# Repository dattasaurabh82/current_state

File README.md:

# World Theme Music Player

<p align="left">
  If you find this project useful, consider supporting its development <br><br>

</p>

---
<br>

> **An AI-powered ambient music generator that transforms daily world news into mood-based soundscapes. Designed to sit on top of IKEA FREKVANS SPEAKERS, this will trigger playback of AI generated soundscape/music when a person enters a room or a motion is detected. So a suitable place for this are contemplation rooms like bathrooms 🙃**

<br>

*What does it look like?*

*Monitor Web Dashboard*

The main functionality of the system is to fetch news headlines from multiple regions, analyze their emotional tone using an LLM, select musical archetypes, and generate unique ambient music — all running autonomously on a Raspberry Pi using open-source LLM models hosted on [Replicate](https://replicate.com/). 
With onboard hardware buttons, all functionalities can be triggered and controlled. For example,  disabling radar trigger or shutting down or turning ON the PI or even resetting WiFi for the PI, can all be carried out via the custom PI HAT I designed! (More on that later ...) 

---

## Table of Contents

- [What it does (Summary)?](#what-it-does-summary)
- [Other features](#other-features)
- [What can you do?](#what-can-you-do)
- [How It Works](#how-it-works)
- [Prerequisites](#prerequisites)
  - [Hardware](#1-hardware)
  - [API Accounts](#2-api-accounts)
- [Summary of steps to take](#summary-of-steps-need-to-take-action)
  - [Step 1: Mandatory Update](#step-1-installation-and-basic-setup-mandatory-update)
  - [Step 2: Configuration Reference](#step-2-installation-and-basic-setup-understand-the-configuration-reference)
  - [Step 3: Run Setup Script](#step-3-run-setup-script)
  - [Step 4: Hardware Testing](#step-4-hardware-testing)
  - [Step 5: Installing WiFi Manager](#step-5-installing-wifi-manager)
  - [Step 6: Test Full Pipeline](#step-6-test-full-pipeline)
  - [Step 7: Services Installation](#step-7-services-installation)
- [Web Dashboard](#web-dashboard)
- [Project Structure](#project-structure)
- [License](#license)
- [Supporting Docs](#supporting-docs)
- [Manual Setup (Archive)](#archive-manual-setup-instructions)
- [TODO](#todo)

---

## What it does (Summary)?

- Every night at 3:00 AM, scrapes news and generates a 30-second ambient music piece based on world sentiment (and various other factors)
- Then, if the device detects presence of a person (also notified via LED), it plays back that music in a loop for a predefined time (currently set to 5 mins) and then stops
- While music is playing, the LED is ON. While paused, it turns OFF
- It serves a web monitor where you can see:
  - News Tab: News that were collected
  - Pipeline Tab: view explaining how music was then generated including Music files too
  - Logs Tab: of all process for live preview and debugging of any steps
- If fails to connect to Wifi, it blinks and notifies you
- If any step in the full pipeline (news scraping -> music generation) it shows in logs and if radar detection is disabled the LED also notifies you with blinks

## Other features

- Smart log management and lot of configuration settings
- It also comes with smart installation and uninstallation scripts, detailed documentation and maintenance instructions
- **Optional and not included in documentation**, but it can automatically upload music and crucial data for future analysis, to drop box as well as locally

## What can you do?

- With the press of a button you can turn the system on & off
- With the press of a button you can headlessly setup it's wifi, over a browser
- You can manually trigger the full pipeline: news scraping -> music generation
- You can play/pause and stop the music with buttons
- You can enable or disable radar detection
- You can run tests to understand how the pipeline works
- **Optional and not included in documentation**, but you can also manually backup with a single cmd or set it to do it automatically 

## How It Works

The system has two modes of operation:

### Pipeline Overview

The **automated pipeline** runs daily at 3:00 AM:

> [!Note]
> This 3:00 AM is defined in cronjob settings which can be manually altered but it is defined in the [services/01_install_and_start_services.sh](services/01_install_and_start_services.sh)

| Stage | What Happens |
|-------|--------------|
| **Fetch** | NewsAPI provides headlines in 4 languages (EN, DE, FR, ES) — 4 API requests total |
| **Analyze** | Llama 3 70B extracts mood: valence (-1 to +1), tension (0-1), hope (0-1), energy level |
| **Select** | Rule-based scoring matches the mood profile to one of 6 musical archetypes |
| **Build** | Three-layer prompt construction: archetype structure + theme textures + daily variety |
| **Generate** | MusicGen stereo-melody-large creates a 30-second ambient piece |
| **Process** | Fade-in (1.5s) and fade-out (2s) are applied |

The **user-triggered interactions** happen via hardware:

| Trigger | Action |
|---------|--------|
| **GPIO17 Button** | Manually triggers the full news→music pipeline |
| **Radar Motion** | Starts looping playback when presence is detected (see [Radar Behavior](#radar-behavior)) |
| **Radar Enable Switch** | GPIO6 toggle — when ON, radar controls playback; when OFF, radar is ignored |
| **Play/Pause Button** | Toggle playback state |
| **Stop Button** | Stop playback completely |

---

## Prerequisites

### 1. Hardware

| ASSEMBLY RENDER | PCB RENDER |
| --- | --- |
|  |  | 

#### Schematic 

>[!Important]
> Click on the ☝🏻 image to see the [detailed schematic](docs/pi-hat-schematic.pdf)

**Project HW Requirements** (_Highlights_):

- Raspberry pi 3A+ (with 32GB or more micro SD card or storage)
- IKEA FREKVANS Speaker: Find them in eBay
- Short audio cable male-male 3.5 mm
  - Extra Custom PCB for Fingerbot (Extra & Optional)
- [MeanWell RS-15-5 15W 5V 3A Power Supply Module](https://amzn.eu/d/2xTGYza): AC to 5V power supply (internal) for powering the PI from the daily chained power supply, coming from the speakers
- mmWave Radar: [Rd-03D Serial mmWave RADAR](https://amzn.eu/d/4WUBDUL) (_Recommended_) or [RCWL-0516 Switching mmWave RADAR](https://amzn.eu/d/39ujNUH) or both (🙃)
- Custom PI-HAT
- Custom 3D prints

>[!Note]
> For the full assembled product details reach out to hi@dattasaurabh.com 

---

### 2. API Accounts

Before running the setup script, create accounts and gather these credentials:

| Service | What You Need | Where to Get It |
|---------|---------------|-----------------|
| **NewsAPI** | API Key | [newsapi.org/account](https://newsapi.org/account) → Generate API Key |
| **Replicate** | API Token | [replicate.com/account/api-tokens](https://replicate.com/account/api-tokens) |

> [!TIP]
> **Keep these credentials handy** — you'll need them when running `setup.sh` in the next section.

#### Cost Breakdown

| Service | Plan | Usage | Cost |
|---------|------|-------|------|
| **NewsAPI** | Free tier (100 requests/day) | 4 requests/day (one per language) | **Free** |
| **Replicate** | Pay-per-use | ~1 generation/day | **~$3/month** |

**Replicate cost details:**
- MusicGen runs on Nvidia A100 (80GB) @ $0.00140/sec — typical generation takes ~50-60 seconds = ~$0.07-0.08
- Llama 3 70B runs on Nvidia A100 (80GB) @ $0.00140/sec — typical analysis takes ~10-15 seconds = ~$0.01-0.02
- **Total per generation: ~$0.08-0.10**

**NewsAPI notes:**
- Uses the `/everything` endpoint to fetch recent articles
- Free tier provides access to articles from the previous day
- Once set to run autonomously, our system makes only 4 requests daily (one per language: EN, DE, FR, ES), well under the 100/day limit

---

## Summary of steps need to take action

> Once you have the HW ready, here's what needs to be done ...

1. Basic Pi setup (update packages)
2. Understand configuration options
3. Run setup script (handles most installation and configuration automatically)
4. Reboot
5. Test hardware
6. Install WiFi manager (optional)
7. Test full pipeline
8. Deploy services

---

### Step 1: Installation and basic setup: Mandatory Update

```bash
sudo apt-get update -y
sudo apt-get upgrade -y
```

After that, reboot. 

---

### Step 2: Installation and basic setup: Understand the Configuration Reference

> [!Note]
> Familiarize yourself with the configuration files. Many of these will be prompted to you during running the helper setup script (below), but understanding them is also important later testing steps.

> In `settings.json` (you may only see now `settings.json.template`)

Controls GPIO pins, hardware behavior, and feature settings:

```json
{
  "inputPins": {
    "playPauseBtnPin": 22,
    "stopBtnPin": 27,
    "runFullCycleBtnPin": 17,
    "radarEnablePin": 6,
    "radarModel": "RCWL-0516",
    "radarPin": 16
  },
  "outputPins": {
    "playerStateLEDPin": 25,
    "radarStateLEDPin": 23
  },
  "hwFeatures": {
    "btnDebounceTimeMs": 0.05,
    "maxLEDBrightness": 25,
    "pauseBreathingFreq": 0.25,
    "motionTriggeredPlaybackDurationSec": 300,
    "cooldownAfterUserActionSec": 60,
    "radarMaxRangeMeters": 2.5,
    "radarTargetTimeoutSec": 1.0
  },
  "music": {
    "fadeInDurationSec": 1.5,
    "fadeOutDurationSec": 2.0
  }
}
```

#### 0. Key Settings Explained `settings.json`

> [!Note]
> The setup script, if ran will update few of these values after asking you and others will remain fixed, especially Hardware ones. But you can also manually create settings file (`cp settings.json.template settings.json`) and edit some of these, if you know what you are doing 🙃. The below explanation thus aims to provide some clarity.     

| Setting | Default | Description |
|---------|---------|-------------|
| `radarEnablePin` | 6 | GPIO pin for radar enable switch — when HIGH, radar triggers playback |
| `radarModel` | `RCWL-0516` | Radar type: `RCWL-0516` (GPIO) or `RD-03D` (Serial UART) |
| `motionTriggeredPlaybackDurationSec` | 300 | How long music plays after motion detected (5 minutes) |
| `cooldownAfterUserActionSec` | 60 | After user presses pause/stop, radar is ignored for this duration |
| `radarMaxRangeMeters` | 2.5 | Detection range (`RD-03D` only) |
| `radarPin` | 16 | GPIO pin to which radar `RCWL-0516` is connected. Not used by radar `RD-03D` as it operates over Serial  |
| `maxLEDBrightness` | 25 | LED brightness (0-100) |

**Notes on diff radars used**: ...

| Radar Model | How to Identify? | Setting | Notes |
| --- | --- | --- | --- |
| [Rd-03D Serial mmWave RADAR](https://amzn.eu/d/4WUBDUL) |  | `"radarEnablePin": 6` <br>`"radarModel": "RD-03D"` | You can leave `"radarPin": 16` in settings but this radar uses PI's Serial PINs and the script will ignore this setting |
| [RCWL-0516 Switching mmWave RADAR](https://amzn.eu/d/39ujNUH) |  | `"radarEnablePin": 6` <br>`"radarModel": "RCWL-0516"`<br>`"radarPin": 16` | `GPIO 16` receives HIGH or LOW based on motion detection |

#### 1. `news_config.json`

> [!Warning]
> Do not change these

Configures which language regions to fetch news from:

```json
{
  "regions": {
    "English_Speaking": { "language": "en" },
    "German_Speaking": { "language": "de" },
    "French_Speaking": { "language": "fr" },
    "Spanish_Speaking": { "language": "es" }
  }
}
```

> [!Note]
> More regions will be included in the future

#### 2. `.env`

API credentials:

```bash
NEWS_API_KEY="your_newsapi_key"
REPLICATE_API_TOKEN="your_replicate_token"
```

>[!Note]
> Will be set by setup script, if ran and here only for reference. 
> If setup script is not ran, then copy [.env.template](.env.template) to `.env` (`cp copy .env.template copy .env`) and you can add them manually. 

---

### Step 3: Run Setup Script

The setup script automates the entire installation process.

#### First Time Installation (via curl)

```bash
curl -fsSL https://raw.githubusercontent.com/dattasaurabh82/current_state/main/setup.sh | bash
```

Or using wget:

```bash
wget -qO- https://raw.githubusercontent.com/dattasaurabh82/current_state/main/setup.sh | bash
```

#### Re-running Setup (after clone)

If you've already cloned the repository, you can re-run setup locally:

```bash
cd ~/current_state
./setup.sh
```

#### What the Setup Script Does

| Step | Description |
|------|-------------|
| **System Check** | Verifies Raspberry Pi and internet connectivity |
| **Date/Time Sync** | Enables NTP and syncs system clock automatically |
| **System Dependencies** | Installs build tools, libraries (`build-essential`, `libssl-dev`, etc.) |
| **Audio Dependencies** | Installs PortAudio (`libportaudio2`) |
| **UV Package Manager** | Installs [UV](https://github.com/astral-sh/uv) for Python dependency management |
| **GPIO Permissions** | Adds user to `gpio` group |
| **Clone Repository** | Clones project to `~/current_state` (or pulls latest if exists) |
| **Python Dependencies** | Runs `uv sync` to install all Python packages |
| **Hostname** | Sets hostname to `aimusicplayer` (access via `aimusicplayer.local`) |
| **Console Auto-login** | Enables auto-login for user services to start on boot |
| **I2C Disable** | Disables I2C to free GPIO3 for power button |
| **Serial Enable** | Enables serial hardware for RD-03D radar, disables serial console |
| **GPIO Shutdown** | Adds `dtoverlay=gpio-shutdown` to config.txt for power button |
| **Hardware Settings** | Interactive prompts for radar model, playback duration, LED brightness → creates `settings.json` |
| **API Credentials** | Interactive prompts for NewsAPI key and Replicate token → creates `.env` |

> [!IMPORTANT]
> After setup completes, **REBOOT is required** for hostname, I2C, serial, and GPIO shutdown changes to take effect.

---

### Step 4: Hardware Testing

Before installing services, test each component individually to verify wiring and configuration.

> [!NOTE]
> If you installed the WiFi Manager (explained below), **stop it first** before testing buttons and LEDs:
> ```bash
> sudo systemctl stop rpi-btn-wifi-manager.service
> ```

#### Test GPIO Buttons & LEDs

```bash
uv run python tests/01_test_IOs.py
```

**What to expect:**
- Press each button and observe console output confirming the press
- LEDs should light up when tested

**Pins being tested:**

| Component | GPIO |
|-----------|------|
| Play/Pause Button | 22 |
| Stop Button | 27 |
| Full Cycle Button | 17 |
| Radar Enable Switch | 6 |
| Player State LED | 25 |
| Radar State LED | 23 |

#### Test Radar Detection

The radar sensor enables automatic, presence-triggered playback. This is useful for installation scenarios where you want music to play when someone approaches.

| Radar Model | Interface | Best For |
|-------------|-----------|----------|
| `RCWL-0516` | GPIO (digital HIGH/LOW) | Simple presence detection |
| `RD-03D` | Serial (UART) | Distance-based detection with configurable range |

> [!Warning]
> Ensure your radar model is set correctly according to your HW setup in `settings.json` (as explained above)

Run the appropriate tests:

**- For `RCWL-0516` (GPIO-based)**

```bash
uv run python tests/02_test_event_radar.py
```

**What to expect:**
- Walk in front of the sensor
- Console shows "Motion detected" / "Motion stopped"
- Radar LED (GPIO 23) lights up during detection

**- For `RD-03D` (Serial-based)**

```bash
uv run python tests/02_test_serial_radar.py
```

**What to expect:**
- Walk in front of the sensor
- Console shows motion waveform

**- For `RD-03D` (Serial-based _but designed for outputting events_)**

```bash
uv run python tests/03_test_serial_radar_as_event.py
```

**What to expect:**
- Walk in front of the sensor
- Console shows "Motion detected" / "Motion stopped"
- Radar LED (GPIO 23) lights up during detection

#### Tuning RD-03D Radar Detection

The RD-03D radar can produce **false triggers in empty rooms**. This happens because its Kalman filter causes the reported distance to oscillate in a slow wave pattern (e.g. 6m → 2m → 6m over ~10 seconds). When the wave dips below `radarMaxRangeMeters`, the old logic counted it as motion.

The detection algorithm now uses a **stability filter** that requires multiple consecutive in-range readings with stable (clustered) distances before triggering. This eliminates false triggers from the oscillating wave while still detecting real people within ~500ms.

**Tunable constants** are at the top of `lib/radar_controller.py`:

| Constant | Default | What it does |
|----------|---------|-------------|
| `RD03D_CONSECUTIVE_READINGS_REQUIRED` | 5 | How many in-range readings in a row before triggering. Higher = fewer false triggers but slower detection. |
| `RD03D_MAX_DISTANCE_STD_DEV` | 0.4 | Max allowed standard deviation (meters) across those readings. Lower = stricter, rejects more noise. |

**If you get false triggers in an empty room:**
- Increase `RD03D_CONSECUTIVE_READINGS_REQUIRED` (try 7 or 8)
- Decrease `RD03D_MAX_DISTANCE_STD_DEV` (try 0.3)
- Decrease `radarMaxRangeMeters` in `settings.json` (try 2.0)

**If real people are not detected:**
- Decrease `RD03D_CONSECUTIVE_READINGS_REQUIRED` (try 3 or 4)
- Increase `RD03D_MAX_DISTANCE_STD_DEV` (try 0.5 or 0.6)

**How to debug:**

```bash
cd ~/current_state/tests

# Raw data view — see every field the radar reports
uv run 04_test_radar_diagnostics.py

# Filter comparison — runs OLD vs STABLE logic side by side
uv run 04_test_radar_diagnostics.py --filter
```

In raw mode, observe:
- Empty room: lots of `·` (out of range), occasional `✓` that dips in and out = normal wave noise
- Person present: sustained blocks of `✓` with stable distances = real detection

In filter mode, observe:
- `OLD` triggers in empty room = the bug
- `STABLE` does not trigger in empty room = fix working
- `STABLE` triggers when you walk in = detection still works

> [!Important]
> Later when the **Radar Enable Switch** (GPIO 6) is ON:
> 
> 1. **Motion detected** → Music starts playing in a loop
> 2. **Music plays for 5 minutes** (configurable: `motionTriggeredPlaybackDurationSec`)
> 3. **No motion for 5 min** → Music auto-stops
> 4. **Motion detected again** → Playback resumes

> [!Note]
> **Cooldown behavior:** If a user manually presses **Pause** or **Stop**, the radar is temporarily ignored for 60 seconds (configurable: `cooldownAfterUserActionSec`). This prevents the radar from immediately restarting playback after a deliberate user action.

#### Test Audio Output

Verify the speaker/audio output is working:

```bash
aplay keep_audio_ch_active.wav
```

**What to expect:** You should hear a short tone.

---

### Step 5: Installing WiFi Manager

For headless WiFi configuration without monitor/keyboard, install and configure this project:[rpi-wifi-configurator](https://github.com/dattasaurabh82/rpi-wifi-configurator).

> [!IMPORTANT]
> Install/enable/setup WiFi Manager **after** hardware testing!

#### Step 5.1: Installing WiFi Manager: How it will Work

0. If PI, could not connect to WiFi, you will see the Status LED Blink ... or you can also remove the front panel to long press the network reset button 
1. **Long press** the WiFi reset button (>4 sec)
2. Pi creates an Access Point (`RPI_NET_SETUP`) (_This is Default but you can change during installation, just follow the prompts. But I would recommend not to change_)

| | | | |
| --- | --- | --- | --- |
|  |  |  |  |

1. Connect your phone/laptop to that AP
2. Navigate to `http://10.10.1.1:4000`
3. Enter your WiFi SSID and password
4. Pi connects to your network: NET Status LED breathes and then turns solid for a bit and then turns off completely.

> [!Note]
> You can checkout this project ([rpi-wifi-configurator](https://github.com/dattasaurabh82/rpi-wifi-configurator)) more in details to understand how it works.

#### Step 5.2: Installing WiFi Manager: The actual Installation Process

```bash
curl -fsSL https://raw.githubusercontent.com/dattasaurabh82/rpi-wifi-configurator/main/install.sh | bash
```

> [!Important]
During setup, enter these GPIO settings for this project, as below:

| Setting | Value | Notes |
|---------|-------|-------|
| Button GPIO | **26** | `NET_RESET_BTN` — dedicated WiFi reset button |
| LED GPIO | **24** | `LED_NET` - dedicated WiFI status LED  |

### Network LED Status Indicators

| LED State | Pattern | Meaning |
|-----------|---------|---------|
| **OFF** | No light | Connected to WiFi (normal operation) |
| **SLOW BREATH** | Smooth pulse | Searching for WiFi / attempting connection |
| **FAST BLINK** | Quick on/off | AP mode active (ready for configuration) |
| **SOLID → OFF** | 2 sec solid | Connection successful |

#### Step 5.3: Stopping for Hardware Tests

If you are running hardware tests, stop the WiFi manager service to free up `GPIO 24` and `GPIO 26`

```bash
sudo systemctl stop rpi-btn-wifi-manager.service
```

After testing, you can restart it:

```bash
sudo systemctl start rpi-btn-wifi-manager.service
```

---

### Step 6: Test Full Pipeline

#### Step 6.1: Test Full Pipeline: Generate music without playback to verify API connectivity

> [!Warning]
> For this to work properly make sure you have the `.env` file with correct settings (keys). As said before, you will be prompted to fill in the keys during installation. So there's some prep work but you can also always manually add them after you understand, from above, what is required in this `.env` file and why

```bash
uv run python main.py --fetch true --play false
```

**What to expect:**
- News headlines are fetched and cached to `news_data_YYYY-MM-DD.json`
- LLM analyzes mood (takes ~10-20 seconds)
- MusicGen generates audio (takes ~50-60 seconds)
- Output music saved to `music_generated/world_theme_YYYY-MM-DD_HH-MM-SS.wav`
- Other metadata, to be used by web-monitor (more on that later), are saved in `generation_results/`

#### Step 6.2 (Optional): Test Full Pipeline: Test/Understand each part of news -> music strategy

> [!Note]
> You can also test individual parts to understand how the music gen prompt is created from news by following the guide  from [docs/MUSIC_PROMPT_GENERATION_PIPELINE.md](docs/MUSIC_PROMPT_GENERATION_PIPELINE.md)

#### Step 6.3: Test Full Pipeline: Test Hardware Player

Interactive test with keyboard controls:

```bash
uv run python run_player.py
```

**Controls:**

| Key | Action |
|-----|--------|
| `P` | Play / Pause |
| `S` | Stop |
| `Q` | Quit |

**What to expect:**
- Player finds the latest song in `music_generated/`
- Press `P` to play — LED goes solid
- Press `P` again to pause — LED breathes
- Press `S` to stop — LED turns off

For daemon mode (no keyboard, GPIO buttons only):

```bash
uv run python run_player.py --daemon
```

#### Step 6.4: Test Full Pipeline: Re-enable WiFi Manager

After testing, restart the WiFi manager if you installed it and disable it for hardware testing, let's say:

```bash
# Check status
sudo systemctl status rpi-btn-wifi-manager.service

# Ctrl+c or :q + ENTER may be required ...

sudo systemctl daemon reload
sudo systemctl start rpi-btn-wifi-manager.service
sudo systemctl status rpi-btn-wifi-manager.service

# Then if you are interested in checking the logs, you can:
# tail -F <PATH TO rpi-wifi-configurator>/logs/<LATEST LOG FILE>.log
```

---

### Step 7: Services Installation

Once hardware testing passes, install the background services.

#### Step 7.1: Services Installation: Check Current Status

```bash
./services/00_status.sh
```

#### Step 8.2: Services Installation: Install All Services

```bash
./services/01_install_and_start_services.sh
```

**This installs:**

| Service | Description |
|---------|-------------|
| `music-player.service` | Plays music, handles GPIO buttons, radar detection |
| `full-cycle-btn.service` | GPIO17 button triggers full news→music pipeline |
| `process-monitor-web.service` | Web dashboard on port 7070 |
| nginx | Reverse proxy (access dashboard on port 80) |

#### Step 7.3: Services Installation: Verify Installation

```bash
./services/00_status.sh
```

**Expected output:**

```
User Services

  ● full-cycle-btn.service
  ● music-player.service
  ● process-monitor-web.service

nginx

  ● nginx
  ● config installed
```

#### Step 7.4 (Good to Know): Services Installation: Uninstall Services

```bash
./services/04_stop_and_uninstall_services.sh
```

**What this removes:**
- User systemd services (stopped, disabled, files deleted)
- nginx site configuration
- Cron job for daily generation

**What this does NOT remove:**
- nginx itself (may be used by other sites)
- Project files (your code is safe)
- Generated music and logs

#### Services Scripts Reference

| Script | Purpose |
|--------|----------|
| `00_status.sh` | Check status of all services, nginx, and cron job |
| `01_install_and_start_services.sh` | Install and start all services + cron job |
| `04_stop_and_uninstall_services.sh` | Stop and remove all services + cron job |

#### Full Project Removal

To completely remove the project (services + files + dependencies):

```bash
./remove.sh
```

**What `remove.sh` offers (interactive):**

| Option | What it removes |
|--------|------------------|
| Services | Calls `04_stop_and_uninstall_services.sh` |
| Virtual environment | `.venv/` directory |
| Generated files | `music_generated/`, `logs/`, `generation_results/`, cache files |
| Project directory | Entire `current_state/` folder |
| UV | UV binary and cache (optional) |

> [!WARNING]
> `remove.sh` is interactive and asks for confirmation before each removal step.

#### Useful Commands

```bash
# Check individual service
systemctl --user status music-player.service

# Follow logs in real-time
journalctl --user -u music-player.service -f

# Manually trigger generation
uv run python main.py --fetch true --play false
```

---

## Web Dashboard

A TUI-style web interface for monitoring the pipeline from any device on your network.

### Features

| Tab | Description |
|-----|-------------|
| **News** | Today's headlines grouped by region (from cached JSON) |
| **Pipeline** | Interactive graph: mood analysis → archetypes → prompt components |
| **Logs** | Live streaming logs (like `tail -f` in your browser) |

### Access URLs

| Method | URL |
|--------|-----|
| Via nginx | `http://aimusicplayer.local` |
| Direct | `http://aimusicplayer.local:7070` |

### Where to Find Things

| What | Location |
|------|----------|
| Generated music | `music_generated/` |
| Today's news | `news_data_YYYY-MM-DD.json` |
| Pipeline results | `generation_results/pipeline_results.json` |
| Visualizations | `generation_results/visualizations/` |
| Logs | `logs/` |

📖 **Full documentation:** [`web/README.md`](web/README.md)

---

## Project Structure

```txt
├── README.md
├── LICENSE
├── pyproject.toml
├── uv.lock
├── main.py                      # Pipeline orchestrator
├── run_player.py                # Hardware player daemon
├── run_full_cycle_btn.py        # GPIO17 button handler
├── keep_audio_ch_active.wav     # Speaker keep-alive tone
├── settings.json                # Hardware & feature config (create from template)
├── news_config.json             # News regions config
├── .env                         # API credentials (create from template)
│
├── lib/                         # Core modules
│   ├── news_fetcher.py          # NewsAPI client
│   ├── llm_analyzer.py          # LLM mood extraction
│   ├── archetype_selector.py    # Rule-based archetype scoring
│   ├── music_prompt_builder.py  # 3-layer prompt construction
│   ├── music_generator.py       # MusicGen via Replicate
│   ├── music_post_processor.py  # Fade in/out
│   ├── player.py                # Audio playback engine
│   ├── hardware_player.py       # GPIO buttons, LEDs, radar
│   ├── radar_controller.py      # RCWL-0516 / RD-03D support
│   └── settings.py              # Settings loader
│
├── services/                    # Systemd service management
│   ├── 00_status.sh             # Check all services
│   ├── 01_install_and_start_services.sh
│   ├── 04_stop_and_uninstall_services.sh
│   └── *.service                # Service unit files
│
├── docs/                        # Documentation
│   ├── MUSIC_PROMPT_GENERATION_PIPELINE.md
│   └── pi-hat-schematic.pdf
│
├── web/                         # Dashboard (FastAPI + WebSocket)
├── tests/                       # Hardware test scripts
├── tools/                       # Utilities
├── logs/                        # Runtime logs
├── music_generated/             # Output audio files
├── generation_results/          # Pipeline outputs + visualizations
└── assets/                      # Documentation images
```

---

## License

[Unlicense](LICENSE)

---

## Supporting Docs:

1. [MUSIC_PROMPT_GENERATION_PIPELINE.md](docs/MUSIC_PROMPT_GENERATION_PIPELINE.md)
2. [Tests](tests)
3. [Web View Monitor](web/README.md)
4. [Hardware Schematic](_HW)

---

<details>
<summary><strong>Click to expand</strong> — Manual Setup Instructions - Reference for setup.sh development</summary>

### Manual Date/Time Setup

If NTP sync fails or you need to set timezone manually:

First, verify your Pi's date is correct:

```bash
date
```

If incorrect, fix via `raspi-config`:

```bash
sudo raspi-config
```

| Step | View |
|------|------|
| Select "Localisation Options" → ENTER |  |
| Select "Timezone" → ENTER |  |
| Select your region |  |

Tab to `<Finish>` and reboot:

```bash
sudo reboot
```

### Install System Dependencies

```bash
sudo apt update -y
sudo apt upgrade -y 
sudo apt install git -y 
sudo apt install build-essential libssl-dev zlib1g-dev libbz2-dev libreadline-dev libsqlite3-dev curl libncursesw5-dev xz-utils tk-dev libxml2-dev libxmlsec1-dev libffi-dev liblzma-dev jq tree -y
sudo apt install python3-dev -y
```

### Install Audio Dependencies

```bash
sudo apt-get install libportaudio2 -y
```

### Install UV

```bash
curl -LsSf https://astral.sh/uv/install.sh | sh
```

### GPIO Permissions

```bash
sudo usermod -a -G gpio $USER
sudo reboot
```

### Clone & Install

```bash
git clone https://github.com/YOUR_USERNAME/current_state.git
cd current_state
uv sync
```

If RPi.GPIO fails:
```bash
uv pip install RPi.GPIO --break-system-packages
```

### Create Environment File

```bash
cp .env.template .env
nano .env
```

Add your credentials:
```bash
NEWS_API_KEY="your_newsapi_key"
REPLICATE_API_TOKEN="your_replicate_token"
```

### Manual Service Installation (Legacy)

If not using the install script:

```bash
# Create user systemd directory
mkdir -p ~/.config/systemd/user

# Music Player
cp services/music-player.service ~/.config/systemd/user/
systemctl --user daemon-reload
systemctl --user enable --now music-player.service

# Full Cycle Button
cp services/full-cycle-btn.service ~/.config/systemd/user/
systemctl --user enable --now full-cycle-btn.service

# Enable linger (services run without login)
sudo loginctl enable-linger $USER
```

### Shutdown & Wake Button (GPIO3)

Enable hardware shutdown/wake using a dedicated button on GPIO3.

#### Step 1: Disable I2C

> [!WARNING]
> GPIO3 is shared with I2C SCL. You must disable I2C to use it for shutdown.

```bash
sudo raspi-config
```

| Step | View |
|------|------|
| Select *Interface Options* |  |
| Select *I2C* |  |
| Select *No* to disable |  |
| *Finish* and reboot |  |

#### Step 2: Enable gpio-shutdown Overlay

```bash
sudo nano /boot/firmware/config.txt
```

Add after the overlays comment section:

```ini
dtoverlay=gpio-shutdown
```

Reboot and test:
- Press GPIO3 button → Pi shuts down
- Press again → Pi wakes up

</details>

---

## TODO

- Add Dropbox backup details in readme (optional feature)
- ~~Serial Radar detection algo improvement~~ ✅ Stability filter (consecutive + std dev)

- 3rd attempt hardware update steps: 
  - 🟠 Speaker Switch switcher 
  - 🟠 Assemble new one ... 

**Future**:
- Add more news regions
- More archetypes
- Embedding models if needed
- Data viz after a period of time on the world sentiment shifts

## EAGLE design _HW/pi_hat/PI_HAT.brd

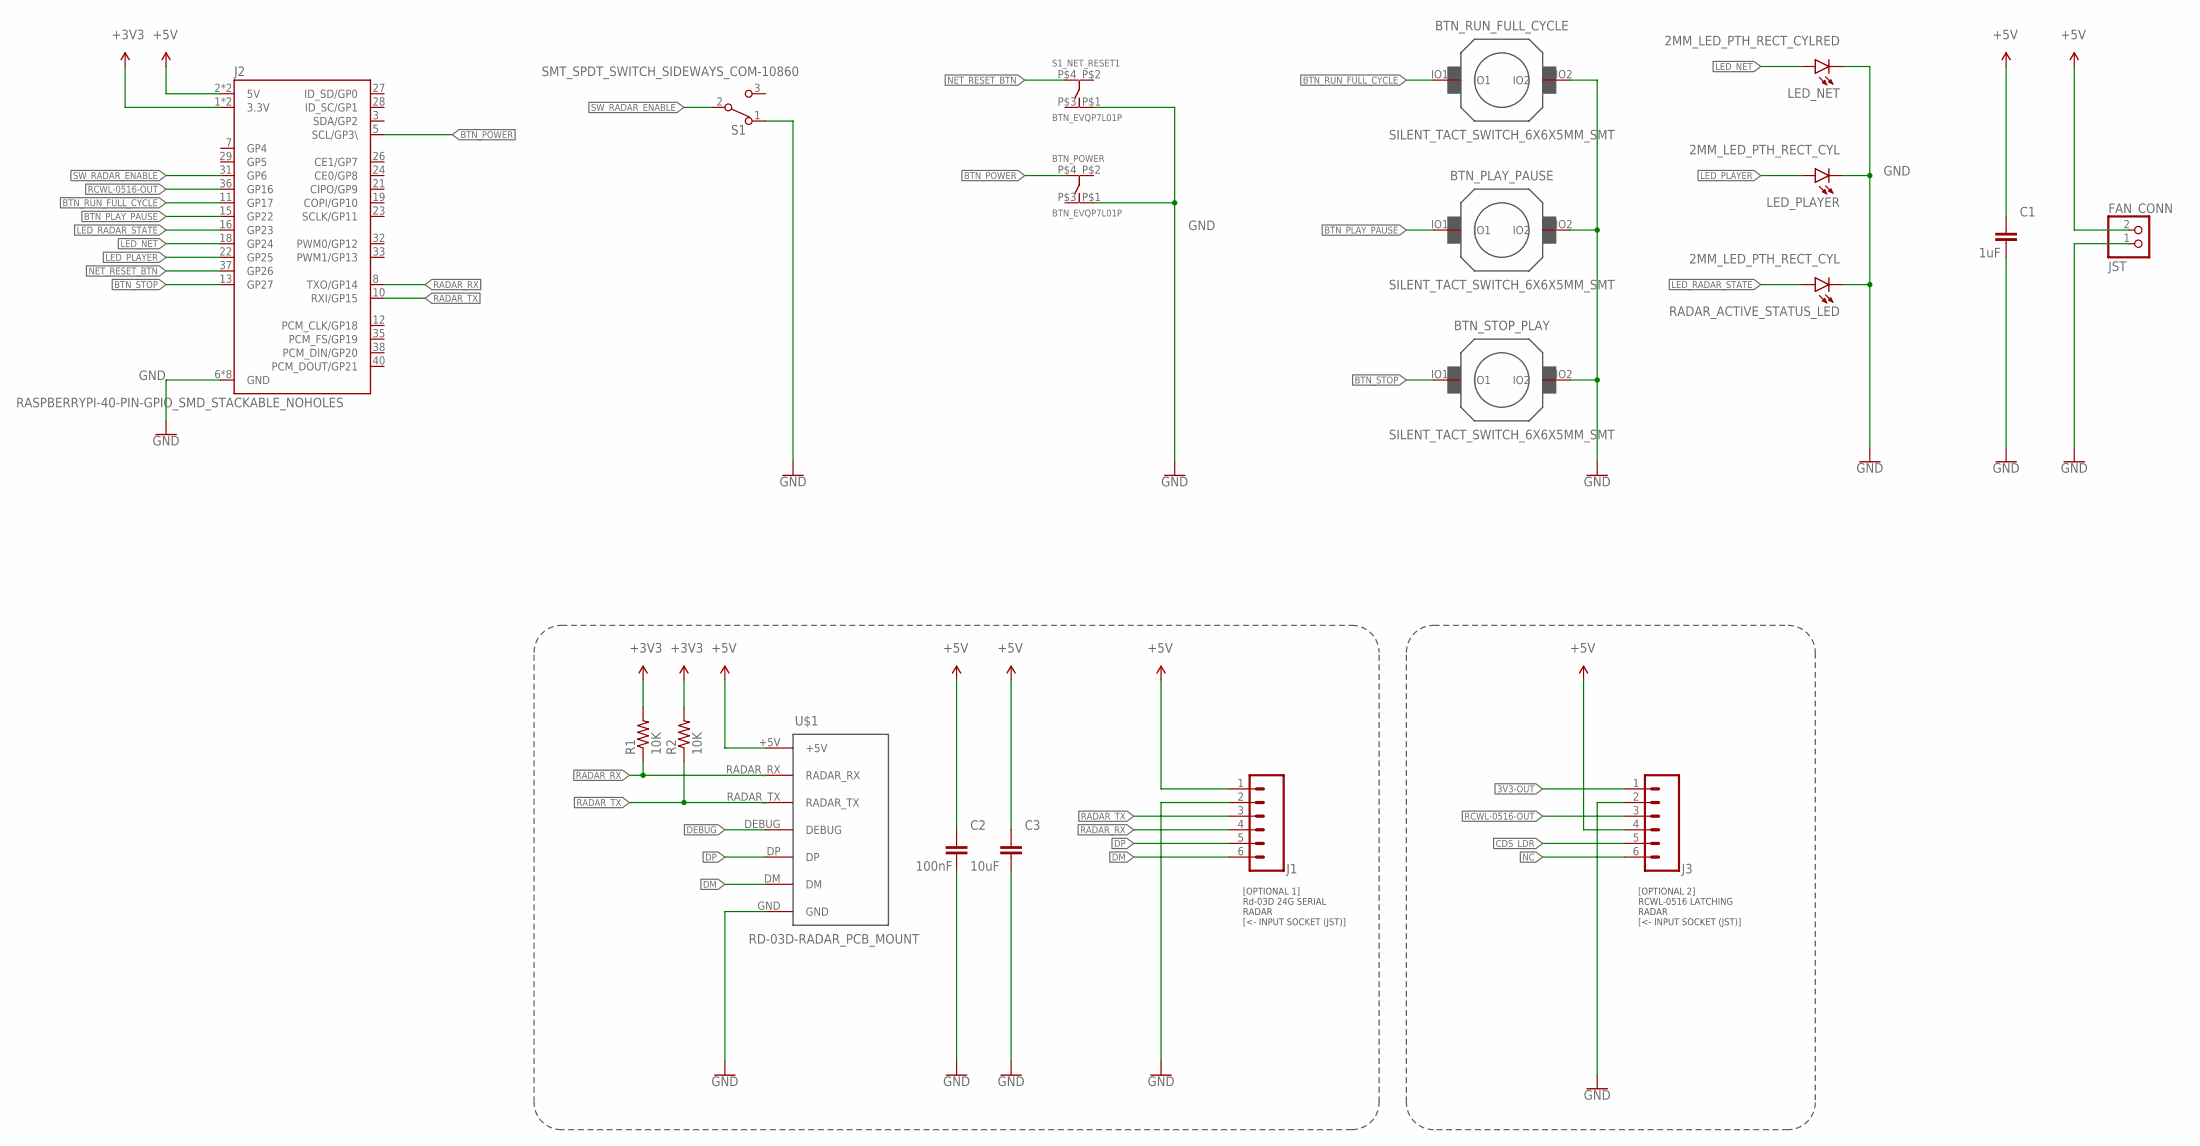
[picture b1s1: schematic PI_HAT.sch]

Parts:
BTN_PLAY_PAUSE: SILENT_TACT_SWITCH_6X6X5MM_SMT
BTN_POWER: BTN_EVQP7L01P
BTN_RUN_FULL_CYCLE: SILENT_TACT_SWITCH_6X6X5MM_SMT
BTN_STOP_PLAY: SILENT_TACT_SWITCH_6X6X5MM_SMT
C1: 1uF; CAPC2012X110
C2: 100nF; CAPC2012X110
C3: 10uF; CAPC2012X110
FAN_CONN: JST; JST_2.5MM_SMT
J1, J3: JST_6PIN_1MMSMD-1MM; JST_6PIN_1MM
J2: RASPBERRYPI-40-PIN-GPIO_SMD_STACKABLE_NOHOLES; RASPBERRY_PI_HAT_40_PIN_PTH_WITH_REFERNCE
LED_NET: 2MM_LED_PTH_RECT_CYLRED; 2MM_LED_PTH_RECT_CYL_RED
LED_PLAYER: 2MM_LED_PTH_RECT_CYL; 2MM_LED_PTH_RECT_CYL_YELLOW
R1, R2: 10K; RESC1608X60
RADAR_ACTIVE_STATUS_LED: 2MM_LED_PTH_RECT_CYL; 2MM_LED_PTH_RECT_CYL_YELLOW
S1: SMT_SPDT_SWITCH_SIDEWAYS_COM-10860; SMT_SPDT_SWITCH_SIDEWAYS
S1_NET_RESET1: BTN_EVQP7L01P
U$1: RD-03D-RADAR_PCB_MOUNT

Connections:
3V3-OUT: J3.1
+3V3: J2.1 (3.3V), J2.17 (3.3V), R1.2, R2.2
+5V: C1.1, C2.1, C3.1, FAN_CONN.2 (1), J1.1, J2.2 (5V), J2.4 (5V), J3.4, U$1.+5V
BTN_PLAY_PAUSE: BTN_PLAY_PAUSE.IO1, J2.15 (GP22)
BTN_POWER: BTN_POWER.P$4, J2.5 (SCL/GP3\)
BTN_RUN_FULL_CYCLE: BTN_RUN_FULL_CYCLE.IO1, J2.11 (GP17)
BTN_STOP: BTN_STOP_PLAY.IO1, J2.13 (GP27)
CDS_LDR: J3.5
DEBUG: U$1.DEBUG
DM: J1.6, U$1.DM
DP: J1.5, U$1.DP
GND: BTN_PLAY_PAUSE.IO2, BTN_POWER.P$1 (1), BTN_RUN_FULL_CYCLE.IO2, BTN_STOP_PLAY.IO2, C1.2, C2.2, C3.2, FAN_CONN.1 (2), J1.2, J2.6 (GND), J2.9 (GND), J2.14 (GND), J2.20 (GND), J2.25 (GND), J2.30 (GND), J2.34 (GND), J2.39 (GND), J3.2, LED_NET.K (CATHODE), LED_PLAYER.K (CATHODE), RADAR_ACTIVE_STATUS_LED.K (CATHODE), S1.1 (NC), S1_NET_RESET1.P$1 (1), U$1.GND
LED_NET: J2.18 (GP24), LED_NET.A (ANODE)
LED_PLAYER: J2.22 (GP25), LED_PLAYER.A (ANODE)
LED_RADAR_STATE: J2.16 (GP23), RADAR_ACTIVE_STATUS_LED.A (ANODE)
NC: J3.6
NET_RESET_BTN: J2.37 (GP26), S1_NET_RESET1.P$4
RADAR_RX: J1.4, J2.8 (TXO/GP14), R1.1, U$1.RADAR_RX
RADAR_TX: J1.3, J2.10 (RXI/GP15), R2.1, U$1.RADAR_TX
RCWL-0516-OUT: J2.36 (GP16), J3.3
SW_RADAR_ENABLE: J2.31 (GP6), S1.2 (COM)

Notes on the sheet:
[OPTIONAL 2] RCWL-0516 LATCHING RADAR [<- INPUT SOCKET (JST)]
[OPTIONAL 1] Rd-03D 24G SERIAL RADAR [<- INPUT SOCKET (JST)]

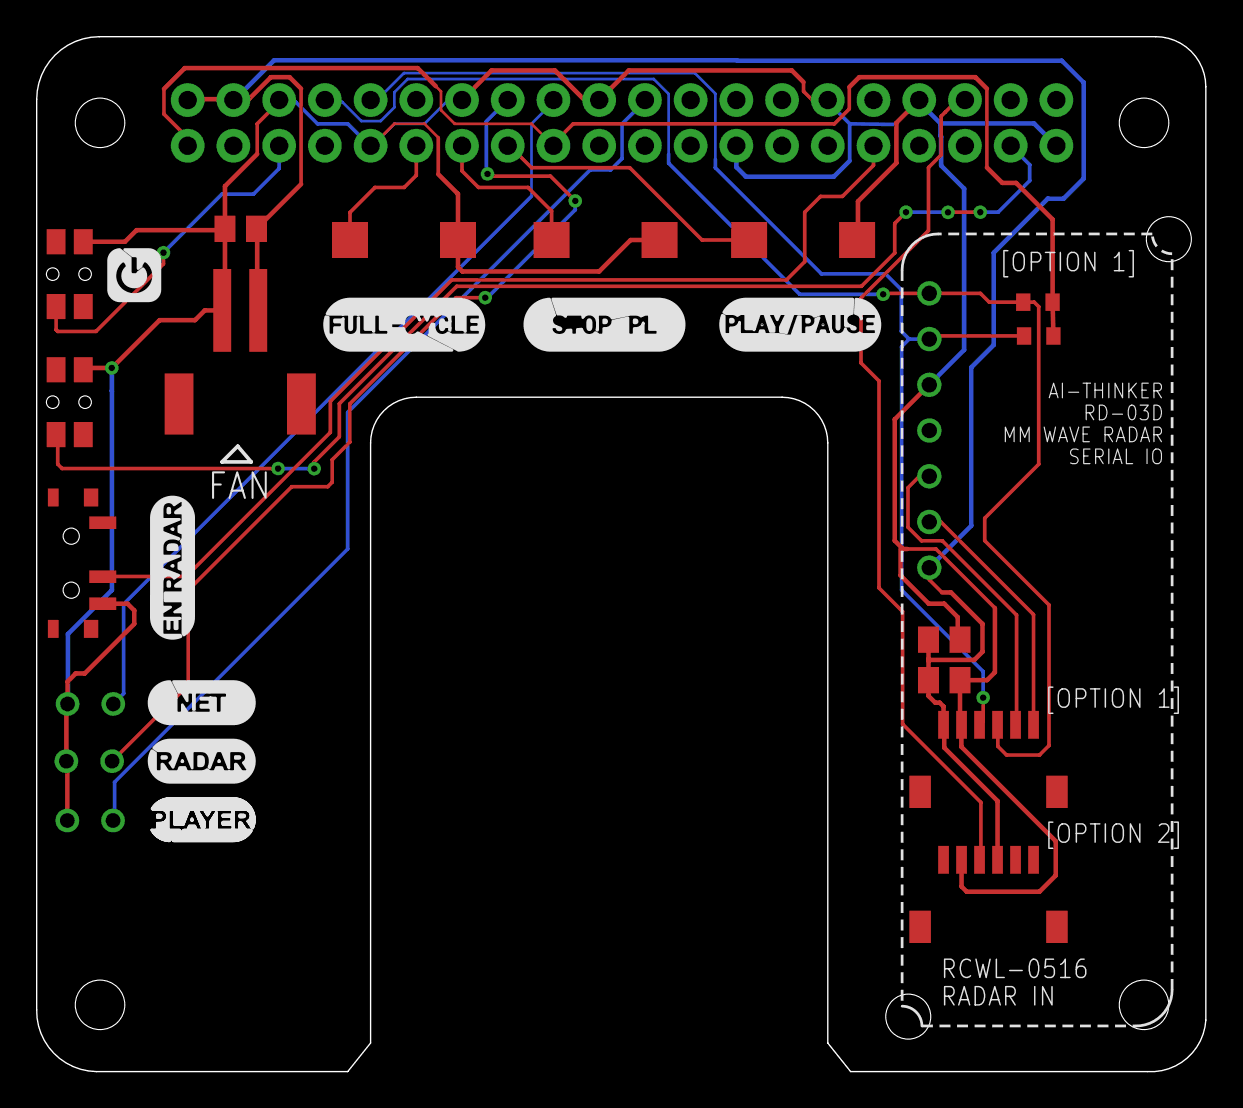
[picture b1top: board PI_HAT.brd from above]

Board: 2 copper layers, 65.0 x 57.5 mm, 19 parts (0 on the bottom side), 17 nets.

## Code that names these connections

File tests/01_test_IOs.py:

#!/usr/bin/env python3
"""
Test Script to verify GPIO connections for LEDs, Buttons, and Switches on Raspberry Pi.
"""

import RPi.GPIO as GPIO
import time
import sys
sys.path.insert(0, str(__file__).rsplit('/', 2)[0])  # Add project root to path
from lib.settings import load_settings

# Load settings
settings = load_settings()

# --- CONFIGURATION ---
LEDS = {
    "LED_NET": 24,  # Hardcoded - used by another project
    "LED_PLAYER": settings["outputPins"]["playerStateLEDPin"],
    "LED_RADAR_STATE": settings["outputPins"]["radarStateLEDPin"],
}

# Note: Buttons connect to GND.
# Code looks for LOW signal (Falling edge).
BUTTONS = {
    "NET_RESET_BTN": 26,  # Hardcoded - used by another project
    "BTN_POWER": 3,  # Hardcoded - used by Kernal (Follow README instructions)
    "BTN_RUN_FULL_CYCLE": settings["inputPins"]["runFullCycleBtnPin"],
    "BTN_PLAY_PAUSE": settings["inputPins"]["playPauseBtnPin"],
    "BTN_STOP": settings["inputPins"]["stopBtnPin"],
}

SWITCHES = {
    "SW_RADAR_ENABLE": settings["inputPins"]["radarEnablePin"],
}


# --- SETUP ---
def setup_gpio():
    GPIO.setmode(GPIO.BCM)
    GPIO.setwarnings(False)  # Handle I2C pin warnings gracefully

    # LEDs: Output, Start Low
    for name, pin in LEDS.items():
        GPIO.setup(pin, GPIO.OUT)
        GPIO.output(pin, GPIO.LOW)

    # Inputs: Input, Pull Up
    # (Pin is held at 3.3V internally. Connecting to GND pulls it LOW)
    all_inputs = {**BUTTONS, **SWITCHES}
    for name, pin in all_inputs.items():
        GPIO.setup(pin, GPIO.IN, pull_up_down=GPIO.PUD_UP)


# --- TESTS ---


def test_leds():
    print("\n" + "=" * 40)
    print("PHASE 1: LED VISUAL CHECK")
    print("=" * 40)
    print("Verify LEDs blink in order...")
    time.sleep(4)

    for name, pin in LEDS.items():
        print(f" -> Blinking {name} (GPIO {pin})...")
        GPIO.output(pin, GPIO.HIGH)
        time.sleep(5)
        GPIO.output(pin, GPIO.LOW)
        time.sleep(2)

    # We ask, but we don't stop the script. Just record the report.
    ans = input("\nDid they look okay? (y/n): ").strip().lower()
    return ans == "y"


def test_buttons():
    print("\n" + "=" * 40)
    print("PHASE 2: BUTTON INPUT CHECK")
    print("=" * 40)
    print("NOTE: If a button is broken, press 'Ctrl+C' to SKIP it.\n")

    results = {}

    for name, pin in BUTTONS.items():
        print(f"Waiting for press: [ {name} ] on GPIO {pin}...")

        try:
            # 1. Wait for Press (LOW)
            while GPIO.input(pin) == GPIO.HIGH:
                time.sleep(0.05)

            # 2. Debounce/Confirm
            time.sleep(0.05)
            if GPIO.input(pin) == GPIO.LOW:
                print(f"   >>> SUCCESS: {name} detected!")
                results[name] = True

            # 3. Wait for Release (HIGH) so we don't accidentally trigger the next one
            while GPIO.input(pin) == GPIO.LOW:
                time.sleep(0.05)

        except KeyboardInterrupt:
            # This catches Ctrl+C
            print(f"   >>> SKIPPING {name} (User Interrupt)")
            results[name] = False
            # We must wait a tiny bit to clear the interrupt signal
            time.sleep(0.5)

    return results


def test_switch():
    print("\n" + "=" * 40)
    print("PHASE 3: SWITCH CHECK")
    print("=" * 40)

    name = "SW_RADAR_ENABLE"
    pin = SWITCHES[name]

    # Dynamic Logic: Check current state first
    is_currently_high = GPIO.input(pin)

    # Determine what to tell the user
    current_status = "OFF (Open)" if is_currently_high else "ON (Closed)"
    target_action = "CLOSE (Turn ON)" if is_currently_high else "OPEN (Turn OFF)"

    print(f"Switch '{name}' is currently: {current_status}")
    print(f"ACTION REQUIRED: Please {target_action} the switch.")

    try:
        # Wait for the state to flip to the opposite of what it started as
        while GPIO.input(pin) == is_currently_high:
            time.sleep(0.05)

        print(f"   >>> SUCCESS: Switch toggle detected!")
        return True

    except KeyboardInterrupt:
        print(f"   >>> SKIPPED Switch Test")
        return False


# --- MAIN ---
def main():
    try:
        setup_gpio()

        # Run Tests
        led_result = test_leds()
        time.sleep(1)
        btn_results = test_buttons()
        time.sleep(1)
        sw_result = test_switch()
        time.sleep(1)

        # Final Report
        print("\n\n")
        print("########################################")
        print("#             TEST REPORT              #")
        print("########################################")

        # LED Report
        print(f"LEDS VISUAL:       {'[PASS]' if led_result else '[FAIL]'}")

        # Button Report
        for name, res in btn_results.items():
            status = "[PASS]" if res else "[FAIL/SKIP]"
            print(f"{name:<18} {status}")

        # Switch Report
        print(f"SW_RADAR_ENABLE:   {'[PASS]' if sw_result else '[FAIL/SKIP]'}")
        print("########################################\n")

    except Exception as e:
        print(f"\nAn error occurred: {e}")
    finally:
        GPIO.cleanup()


if __name__ == "__main__":
    main()

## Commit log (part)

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2025-09-19 play pause and toto update
2025-09-19 play pause WIP
2025-09-19 loguru
2025-09-19 Updated ToDo
2025-09-29 testing new logger
2025-09-29 local comits do not push
2025-09-29 added silent wav file
2025-09-29 adding silent audio handler
2025-09-29 added pigpio lib
2025-09-29 adding gpio capabilities
2025-09-29 added button ctrls - working
2025-09-29 wip: silent signal crash handling...
2025-09-29 Dockerization WIP
2025-09-29 env file "" issue test
2025-09-30 cleanup test
2025-09-30 daemon to avoid keyboard interaction
2025-11-16 added HW files - INITIAL EXPORTS
2025-12-02 updated test script
2025-12-02 added, in pi, GPIO check tests. Next (TBD): incl. serial radar test
2025-12-02 renamed
2025-12-04 Added some svgs
2025-12-18 updated curr pin-outs as per pcb
2025-12-18 Added boot management instructions after testing
2026-01-05 increased silent active channel audio clip parallel playback
2026-01-05 rebase
2026-01-05 Fix keep_audio_alive to properly wait for silent audio playback to finish before stopping
2026-01-05 Improve keep_audio_alive to allow silent audio stream to drain before stopping
2026-01-05 Increase keep-alive interval to 90 seconds for improved silent audio playback
2026-01-05 Add .env.template with placeholders for API keys and tokens
2026-01-05 Enhance output formatting for file listings in backup script
2026-01-05 Add cleanup check for local music folder size in backup script
2026-01-05 Fix upload logic to ensure backup completion message is displayed correctly
2026-01-05 Fix cleanup logic to enable deletion of old .wav files in the music folder
2026-01-05 Update cron job schedule to run backup script at 2:40 AM
2026-01-05 Remove commented-out keep_audio_alive function and its associated logic
2026-01-05 Refactor code structure for improved readability and maintainability
2026-01-06 Update .env.template with correct placeholder values for API keys and tokens
2026-01-06 Refactor refresh_token function to clarify variable naming and improve token retrieval logging
2026-01-06 reset to working step
2026-01-06 reset to old state
2026-01-06 Add initial test implementation for RCWL-0516 Doppler Radar Sensor
2026-01-06 [test] lgpio lib instead for rpi-gpio for edge detection without sudo
2026-01-06 Enhance RCWL-0516 radar sensor test by adding LED state indication and improving output clarity
2026-01-06 Adjust LED brightness levels and simplify breathing effect in HardwarePlayer
2026-01-06 Reduce LED brightness levels in HardwarePlayer for improved visibility and effect
2026-01-06 Refactor region configuration by renaming config file and updating load function
2026-01-06 local latest news added in pi
2026-01-07 increased pause state breathing effect param
2026-01-07 added a new script
2026-01-07 adding various exit codes for exceptions in full process
2026-01-07 Fix Key names
2026-01-07 [TEST] added led for process status
2026-01-07 added run full cycle script systemd unit file
2026-01-07 added full path of uv
2026-01-07 organizing ...
2026-01-07 refactor: centralize settings.json config, add GPIO button trigger for full cycle, consolidate logs to logs/
2026-01-07 added daemon mode
2026-01-07 added docker cleanup info (for later)
2026-01-07 config: add motion-triggered playback duration and cooldown settings
2026-01-07 feat: integrate radar motion detection with auto-stop timer and cooldown
2026-01-07 fix: radar LED reflects motion state, improve logging, fix RD-03D GPIO error
2026-01-07 fix: log ignored motion triggers during user playback, log cooldown expiry
2026-01-07 added the dynamic status led pin from settings
2026-01-07 feat: add RD-03D serial radar support in RadarController
2026-01-07 added settings as template
2026-01-07 test old event radar again
2026-01-07 removed docker stuff
2026-01-08 feat(music-gen-study): add news analyzer with structured LLM output
    - Create test data files for different scenarios (positive, negative, mixed, edge cases)
    - Implement 01_news_analyzer.py with structured NewsAnalysis output
    - Define constrained mood dimensions: emotional_valence, tension_level, hope_factor, energy_level
    - Add Llama 3 70B integration via Replicate API
    - Include dry-run mode with mock data for testing without API calls
    - Add rich terminal visualization with fallback to basic output
2026-01-08 .env loading fixed for music gen study script (WIP)
2026-01-08 Fixed. The changes:
    Removed JSON example with curly braces from SYSTEM_PROMPT (which goes into the template)
    Added JSON example in the user_prompt (which is substituted into {prompt} placeholder and doesn't get format-string processed)
2026-01-08 fix(music-gen-study): fix news analyzer LLM integration
    - Add dotenv loading from project root for REPLICATE_API_TOKEN
    - Fix JSON format string escaping in prompt template
    - Move JSON example to user prompt to avoid template parsing issues
    - Auto-create output directories when saving analysis
    - Test verified: positive, negative, mixed scenarios + real news data
2026-01-08 feat(music-gen-study): add theme textures, daily variation, and SVG visualizations
    - Create theme_textures.py with 30+ curated theme→texture mappings
    (timbre, movement, harmonic character for nuanced prompts)
    - Add daily variation system (instrument rotation, mood shuffle, tempo nudge)
    - Implement visualizations.py with 3 SVG generators:
    - mood_radar.svg: 4-axis analysis chart
    - archetype_wheel.svg: archetype score visualization
2026-01-08 integrating new music gen approach
2026-01-08 locally tested in opne of the pies
2026-01-09 remove redundant data
2026-01-09 Updating pipeline explanation guide
2026-01-09 Updated readme's ToDos
2026-01-09 feat: implemented uploading of generation data dump to also drop box after each run, based on if it is enabled in settings
2026-01-09 cleanup
2026-01-09 feat: add web dashboard foundation with vendor assets
    - Create web/ folder structure (app, routes, templates, static)
    - Add xterm.js v5.3.0 (terminal emulator for live logs)
    - Add IBM Plex Mono fonts (TUI monospace styling)
    - Add generation_backup.py for Dropbox backup of pipeline results
    - Integrate backup into llm_analyzer.py pipeline
    - Add backup.generation_results_to_dropbox setting
2026-01-09 feat: Enhance TUI with structured logs and dynamic content panels
2026-01-09 Updated readme ToDos
2026-01-09 feat(logs): Implement WebSocket streaming for live log updates
    - Added WebSocket support in logs.py for real-time log streaming.
    - Created LogFileHandler to monitor log files and send updates to connected clients.
    - Integrated log streaming into app.py by including the logs router.
    - Enhanced logs.js to connect to the WebSocket and display logs with color coding based on log levels.
    - Implemented terminal initialization and resizing handling for better user experience.
2026-01-09 feat(web): responsive log grid for mobile/tablet
2026-01-09 feat: Integrate WaveSurfer.js for audio waveform visualization and enhance audio player UI
    - Updated README to reflect hardware update steps with visual indicators.
    - Enhanced audio player styles in CSS for better aesthetics and dark theme support.
    - Added WaveSurfer.js integration for audio waveform visualization in the pipeline.
    - Replaced audio controls with waveform display and play/pause functionality.
    - Implemented real-time audio file updates with polling mechanism.
    - Added JavaScript logic for managing multiple audio waveforms and playback states.
2026-01-09 chore: clean up code structure and remove unused code blocks feat(web): add derivation visualization with vis-network
    - Add /api/derivation endpoint with enriched archetype data
    - Collapsible "How It Works" section at top of Pipeline tab
    - Viz 1: Metric → Archetype matching (weighted edges by score)
    - Viz 2: Archetype → Prompt assembly flow
    - Download vis-network.min.js to vendor/
    - Dark theme styling for graph containers
2026-01-09 feat(web): redesign pipeline tab with full flow visualization
    - Header: "WORLD CURRENT STATE AI MUSIC GEN SYSTEM ✨"
    - Pipeline tab: ALL CAPS, 3-column steps + audio sidebar
    - Full flow viz at bottom showing complete derivation:
    - Metrics → Archetypes (weighted connections)
    - Themes → Layer 2: COLOR (texture selection)
    - Date Seed → Layer 3: VARIETY
2026-01-09 feat(web): enhance pipeline layout with responsive grid and improved styling
2026-01-09 feat(web): improve data display layout and enhance archetype blend ratio visibility
2026-01-10 feat(web): update mobile layout for pipeline and enhance tooltip styling
2026-01-10 fix(docs): update run command in README for correct port configuration
2026-01-10 fix(service): update process monitor service configuration for user and restart policy
2026-01-10 fix(service): change WantedBy target in process monitor service configuration
2026-01-10 fix(docs): update README with nginx permissions and static file path correction
2026-01-10 fix(docs): update ToDo section in README with new tasks and improvements
2026-01-10 fix(docs): remove status indicators from ToDo and Hardware Update Steps in README
2026-01-10 refactor(web): production-grade overhaul of web dashboard codebase
    Python backend:
    - Add proper package structure (__init__.py, py.typed)
    - Add logging throughout with appropriate levels
    - Add comprehensive type hints (Optional[] for 3.9 compat)
    - Extract constants for magic strings/numbers
    - Add detailed docstrings for all functions
2026-01-10 fix: update service configurations and README to reflect new project directory structure
2026-01-10 feat: implement installation and uninstallation scripts for services and nginx configuration
2026-01-10 local commit on pi to refactr harcoded .venv shebang paths
2026-01-10 feat: enhance service status reporting in installation and uninstallation scripts
2026-01-10 feat: add service status check script for diagnostics
2026-01-10 fix: adjust spacing in service status output for better readability
2026-01-10 fix: update file permissions for service scripts to ensure executable access
2026-01-10 fix: update file permissions and add status check execution in install/uninstall scripts
2026-01-10 fix: remove outdated command from quick fix instructions in status script
2026-01-10 docs: update README to clarify setup scripts status and improve readability
2026-01-10 Implement code changes to enhance functionality and improve performance
2026-01-10 Remove outdated news data file for January 9, 2026
2026-01-10 style: update media query for responsive design and add mobile hint for graph visibility
2026-01-10 fix: revert revision number in uv.lock to maintain compatibility
2026-01-10 style: remove mobile/tablet portrait graph hint and related styles for cleaner UI
2026-01-11 docs: Updating README
2026-01-11 feat(setup): Add system configuration and settings.json setup
    README updates:
    - Fix Replicate cost: $0.30 → $3/month
    - Fix NewsAPI requests: 2 → 4 (one per language)
    - Add docs/ folder to project structure
    - Remove manual date/time step (now automated)
    - Renumber steps: 8 → 7
2026-01-11 fix(setup): Fix curl|bash stdin, null bytes, add auto-login
    - Add exec < /dev/tty for interactive prompts when piped
    - Use /proc/cpuinfo instead of /proc/device-tree/model
    - Add console auto-login (do_boot_behaviour B2)
    - Update README documentation
2026-01-11 fix(setup): Wrap script in braces to fix curl|bash pipe issue
    - Wrapping in { } forces bash to read entire script before executing
    - Prevents 'curl: (23) Failure writing output' error
    - exec in bootstrap no longer breaks the pipe prematurely
2026-01-11 fix(setup): Add cloud-init fix to preserve hostname
    - Create /etc/cloud/cloud.cfg.d/99_preserve_hostname.cfg
    - Prevents cloud-init from reverting hostname on boot
2026-01-11 fix: Add cloud-init fix to setup.sh, add system revert to remove.sh
    setup.sh:
    - Create /etc/cloud/cloud.cfg.d/99_preserve_hostname.cfg
    - Prevents cloud-init from reverting hostname on boot
    remove.sh:
    - Add revert_system_config() function
    - Reverts hostname, I2C, serial, auto-login, GPIO shutdown
2026-01-11 fix: Add nginx to system dependencies
2026-01-11 fix: after editing permission was not granted
2026-01-14 Updated ToDo list
2026-01-22 Added funding and sponsorship
